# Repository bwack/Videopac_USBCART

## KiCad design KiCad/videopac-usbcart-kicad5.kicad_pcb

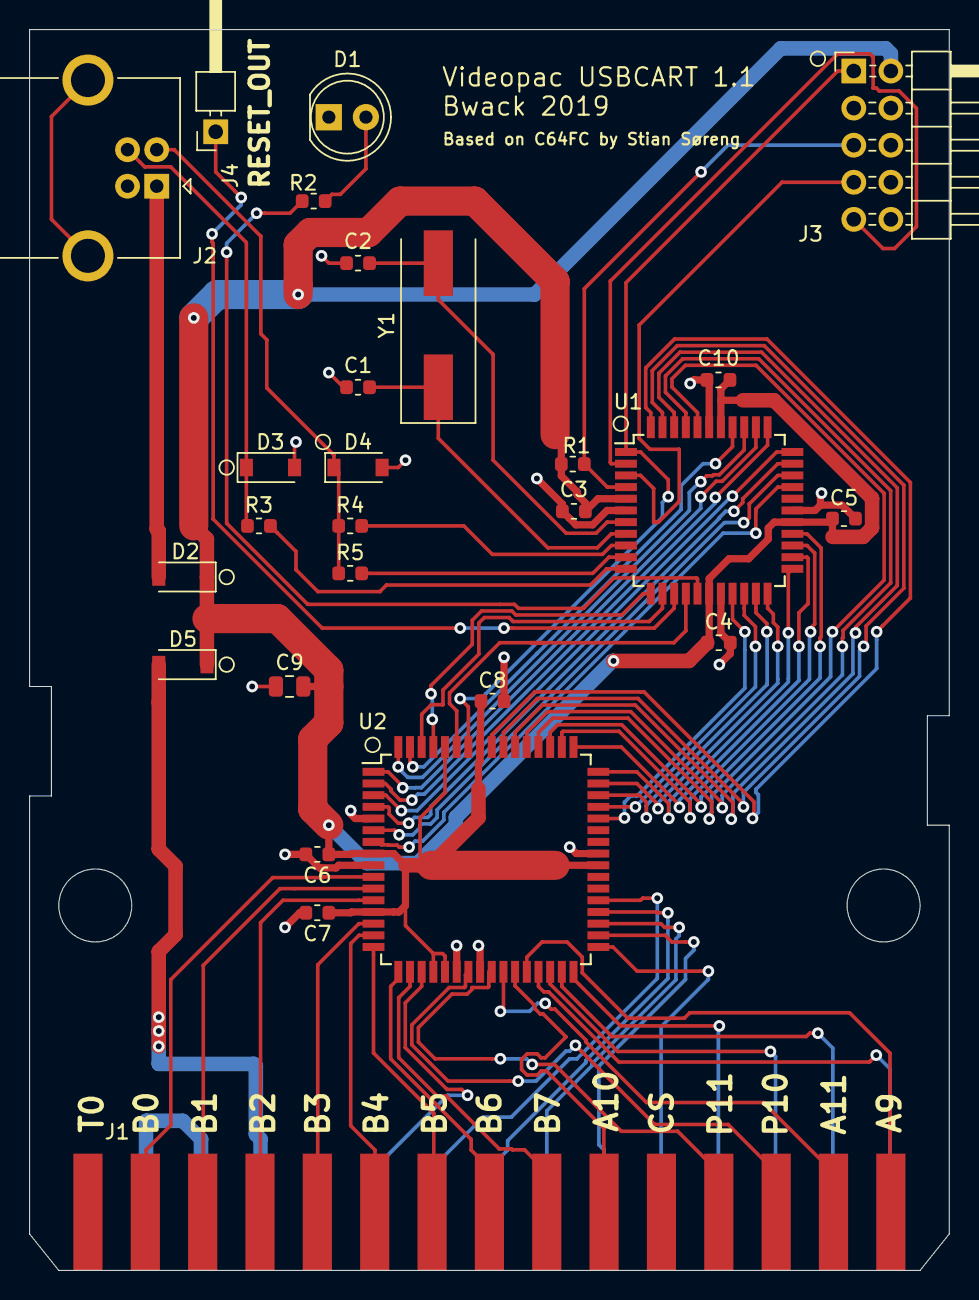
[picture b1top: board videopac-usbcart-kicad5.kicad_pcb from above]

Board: 2 copper layers, 63.0 x 85.0 mm, 27 parts (0 on the bottom side), 65 nets.

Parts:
C1, C2: 22pF; C_0603_1608Metric
C3, C4, C5, C6, C7, C8, C10: 100nF; C_0603_1608Metric
C9: 4u7; C_0805_2012Metric
D1: LED; LED_D5.0mm_Clear
D2, D5: MBR0520; D_SOD-123
D3, D4: BZT52Bxx; D_SOD-123
J1: Videopac-edgeconnector; videopac-edgecon
J2: USB_B; USB_B_OST_USB-B1HSxx_Horizontal
J3: AVR-ISP-10; PinHeader_2x05_P2.54mm_Horizontal
J4: Conn_01x01_Male; PinHeader_1x01_P2.54mm_Horizontal
R1: 4k7; R_0603_1608Metric
R2: 510; R_0603_1608Metric
R3, R4: 68; R_0603_1608Metric
R5: 1k5; R_0603_1608Metric
U1: ATmega16A-AU; TQFP-44_10x10mm_P0.8mm
U2: IDT7006PF-PN64; TQFP-64_14x14mm_P0.8mm
Y1: 12MHz; Crystal_SMD_HC49-SD

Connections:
+5V: C3.1, C4.1, C5.1, C6.1, C7.1, C8.1, C9.2, C10.1, D2.1, D5.1, J3.2, R1.2, U1.5, U1.17, U1.27, U1.38, U2.8, U2.13, U2.20, U2.21, U2.40, U2.57, U2.60
/5V_CART: D5.2, J1.D
/#MCU_CE: U1.15, U2.59
/#MCU_OE: U1.13, U2.62
/#PSEN: J1.F, U2.19
/A0: J1.G, U2.37
/A1: J1.H, U2.36
/A2: J1.J, U2.35
/A3: J1.K, U2.34
/A4: J1.L, U2.33
/A5: J1.M, U2.32
/A6: J1.P, U2.31
/A7: J1.N, U2.30
/A8: J1.R, U2.29
/A9: J1.15, U2.28
/A10: J1.10, U2.27
/A11: J1.14, U2.26
/A12: J1.12, U2.25
/A13: J1.13, U2.23
/D0: J1.2, U2.10
/D1: J1.3, U2.11
/D2: J1.4, U2.12
/D3: J1.5, U2.14
/D4: J1.6, U2.15
/D5: J1.7, U2.16
/D6: J1.8, U2.17
/D7: J1.9, U2.18
/D+: D3.1, J2.3, R3.1
/D-: D4.1, J2.2, R4.1, R5.1
/LED: R2.2, U1.16
/MCU_A0: U1.19, U2.44
/MCU_A1: U1.20, U2.45
/MCU_A2: U1.21, U2.46
/MCU_A3: U1.22, U2.47
/MCU_A4: U1.23, U2.48
/MCU_A5: U1.24, U2.49
/MCU_A6: U1.25, U2.50
/MCU_A7: U1.26, U2.51
/MCU_A8: U1.40, U2.52
/MCU_A9: U1.41, U2.53
/MCU_A10: U1.42, U2.54
/MCU_A11: U1.43, U2.55
/MCU_A12: U1.44, U2.56
/MCU_A13_MOSI: J3.1, U1.1, U2.58
/MCU_D0: U1.37, U2.63
/MCU_D1: U1.36, U2.64
/MCU_D2: U1.35, U2.1
/MCU_D3: U1.34, U2.2
/MCU_D4: U1.33, U2.3
/MCU_D5: U1.32, U2.4
/MCU_D6: U1.31, U2.6
/MCU_D7: U1.30, U2.7
/MCU_MISO: J3.9, U1.2
/MCU_R/#W: U1.12, U2.61
/MCU_RESET: J3.5, R1.1, U1.4
/MCU_SCK: J3.7, U1.3
/TARGET_RESET: J4.1, U1.14
/VBUS: D2.2, J2.1
/VUSB+: R3.2, U1.11
/VUSB-: R4.2, U1.9
/VUSB-2: R5.2, U1.10
/XTAL1: C1.1, U1.8, Y1.1
/XTAL2: C2.1, U1.7, Y1.2
GND: C1.2, C2.2, C3.2, C4.2, C5.2, C6.2, C7.2, C8.2, C9.1, C10.2, D1.1, D3.2, D4.2, J1.B, J1.C, J2.4, J3.4, J3.6, J3.8, J3.10, U1.6, U1.18, U1.28, U1.39, U2.5, U2.9, U2.22, U2.24, U2.41
unnamed: D1.2, R2.1

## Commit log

2019-04-20 First commit v1.0beta
2019-05-05 rev 1.1
